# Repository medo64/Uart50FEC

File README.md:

[UART 5V Framework Expansion Card](https://medo64.com/uart50fec/)
=================================================================

This Framework laptop expansion card will show up on your system as a serial
device and allow for a non-isolated serial UART communication up to 1 Mbaud
baud rate.

Please note that this card is not using RS-232 but 5V TTL.

## UART Pinout

To connect to this board, one has to use a 4-pin JST XH connector. The following
table represents the pinout, pin 1 being on the left as looking into the
expansion card.

| # | Ref | Description                     |
|--:|:---:|---------------------------------|
| 1 | GND | Ground connection               |
| 2 | RXD | Receive (5V TTL)                |
| 3 | TXD | Transmit (5V TTL)               |
| 4 | 5V  | 5V 500mA output (typical)       |

Using 22 AWG wire 0.25 mm² is recommended.

## Supported Speeds

This board employs the FT232R as its UART chip, and consequently, it supports
all the baud rates this chip [can handle](https://ftdichip.com/Documents/AppNotes/AN232B-05_BaudRates.pdf).
The table below lists the standard baud rates.

| Baud rate |    Actual | Error |    Divisor |
|----------:|----------:|------:|-----------:|
|       300 |       300 | 0.00% |  10000.000 |
|       600 |       600 | 0.00% |   5000.000 |
|     1,200 |     1,200 | 0.00% |   2500.000 |
|     1,800 |     1,800 | 0.00% |   1666.625 |
|     2,400 |     2,400 | 0.00% |   1250.000 |
|     4,800 |     4,800 | 0.00% |    625.000 |
|     7,200 |     7,201 | 0.01% |    416.625 |
|     9,600 |     9,600 | 0.00% |    312.500 |
|    14,400 |    14,406 | 0.04% |    208.250 |
|    19,200 |    19,200 | 0.00% |    156.250 |
|    28,800 |    28,812 | 0.04% |    104.125 |
|    38,400 |    38,400 | 0.00% |     78.125 |
|    57,600 |    57,692 | 0.16% |     52.000 |
|   115,200 |   115,385 | 0.16% |     26.000 |
|   230,400 |   230,769 | 0.16% |     13.000 |
|   460,800 |   461,538 | 0.16% |      6.500 |
|   921,600 |   923,077 | 0.16% |      3.250 |
| 1,000,000 | 1,000,000 | 0.00% |      3.000 |

While chip does support baud rates up to 3 Mbaud, granularity of such rates
is severely limited.

---
*You can check my blog and other projects at [www.medo64.com](https://www.medo64.com/electronics/).*

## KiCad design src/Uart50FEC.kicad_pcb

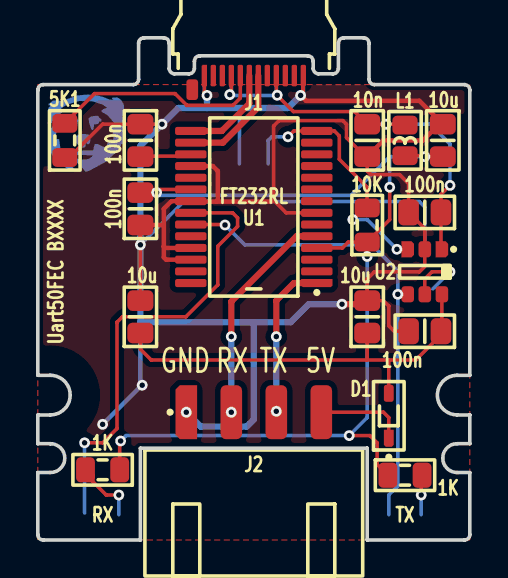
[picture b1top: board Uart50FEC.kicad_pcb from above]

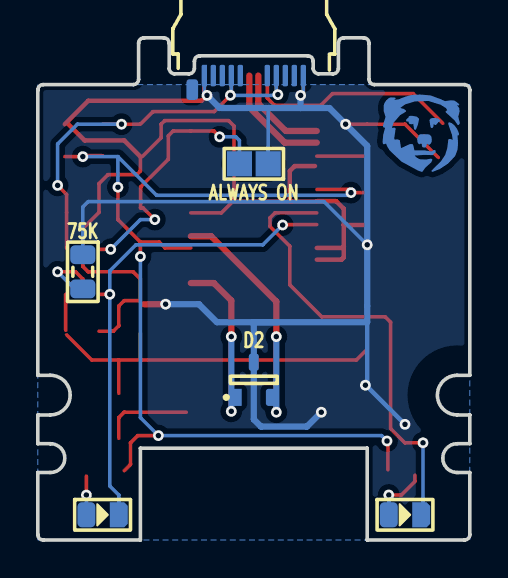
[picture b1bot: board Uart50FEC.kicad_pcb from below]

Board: 2 copper layers, 24.0 x 27.9 mm, 24 parts (6 on the bottom side), 17 nets.

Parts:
C1: 10n; C (0805)
C2, C3, C4, C5: 100n; C (0805)
C6, C7, C8: 10u; C (0805)
D1: CUS08F30; D (SOD323)
D2: SM05T1G; D TVS 5V [SM05T1G] (SOT23-3)
DS1: RX; DS (0805)
DS2: TX; DS (0805)
ICON: Medo64; ICON Medo64
J1: 105444-0001; J USB C 3.2 Edge (24w)
J2: B4B-XH-A; J JST XH Edge [UART] (4w)
JP1: ALWAYS ON; JP (0805)
L1: 600R; L (0805)
R1, R2: 1K; R (0805)
R3: 5K1; R (0805)
R4: 10K; R (0805)
R5: 75K; R (0805)
U1: FT232RL; U Transceiver UART [FT232R] (SSOP-28)
U2: MIC2005A-1; U LoadSwitch Adjustable [AP22652W6-7] (SOT23-6)

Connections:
3V3_UART_USB: C3.2, U1.17
5V: C2.2, C6.2, L1.1, R1.1, R2.1, R4.1, U1.4, U1.20
5V_OUT: D1.1, J2.4
5V_SWITCHED: C5.1, C7.1, C8.1, D1.2, U2.6
5V_USB: C1.2, C4.1, J1.A4, J1.A9, J1.B04, J1.B09, L1.2, U2.1
A_CC: J1.A5, R3.2
GND: C1.1, C2.1, C3.1, C4.2, C5.2, C6.1, C7.2, C8.2, D2.3, J1.A1, J1.A12, J1.B01, J1.B12, J2.1, JP1.2, R3.1, R5.2, U1.7, U1.18, U1.21, U1.25, U1.26, U2.2
ILIM: R5.1, U2.5
LED_RX#: DS1.1, U1.22
LED_RXD': DS1.2, R1.2
LED_TX#: DS2.1, U1.23, U2.4
LED_TXD': DS2.2, R2.2
PWREN#: JP1.1, R4.2, U1.14, U2.3
RXD: D2.2, J2.2, U1.5
TXD: D2.1, J2.3, U1.1
USB_DM: J1.A7, U1.16
USB_DP: J1.A6, U1.15

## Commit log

2024-05-11 Updated type-C connector to allow for more soldermask
2024-06-02 Fixed max power
2024-06-02 Changed pinout
2024-06-06 More output capacitance
2024-06-06 Swapped load switch
2024-06-06 Added jumper for always on
2024-06-06 Lowering output current a bit
2024-06-10 Fixed output enable
2024-06-10 Updated net names
